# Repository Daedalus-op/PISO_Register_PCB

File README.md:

# PCB Designs
- [PISO Shift Register](./PISO_Shift_Registor/README.md)
- [Cascadable Full Adder](./Cascadable_Full_Adder/README.md)

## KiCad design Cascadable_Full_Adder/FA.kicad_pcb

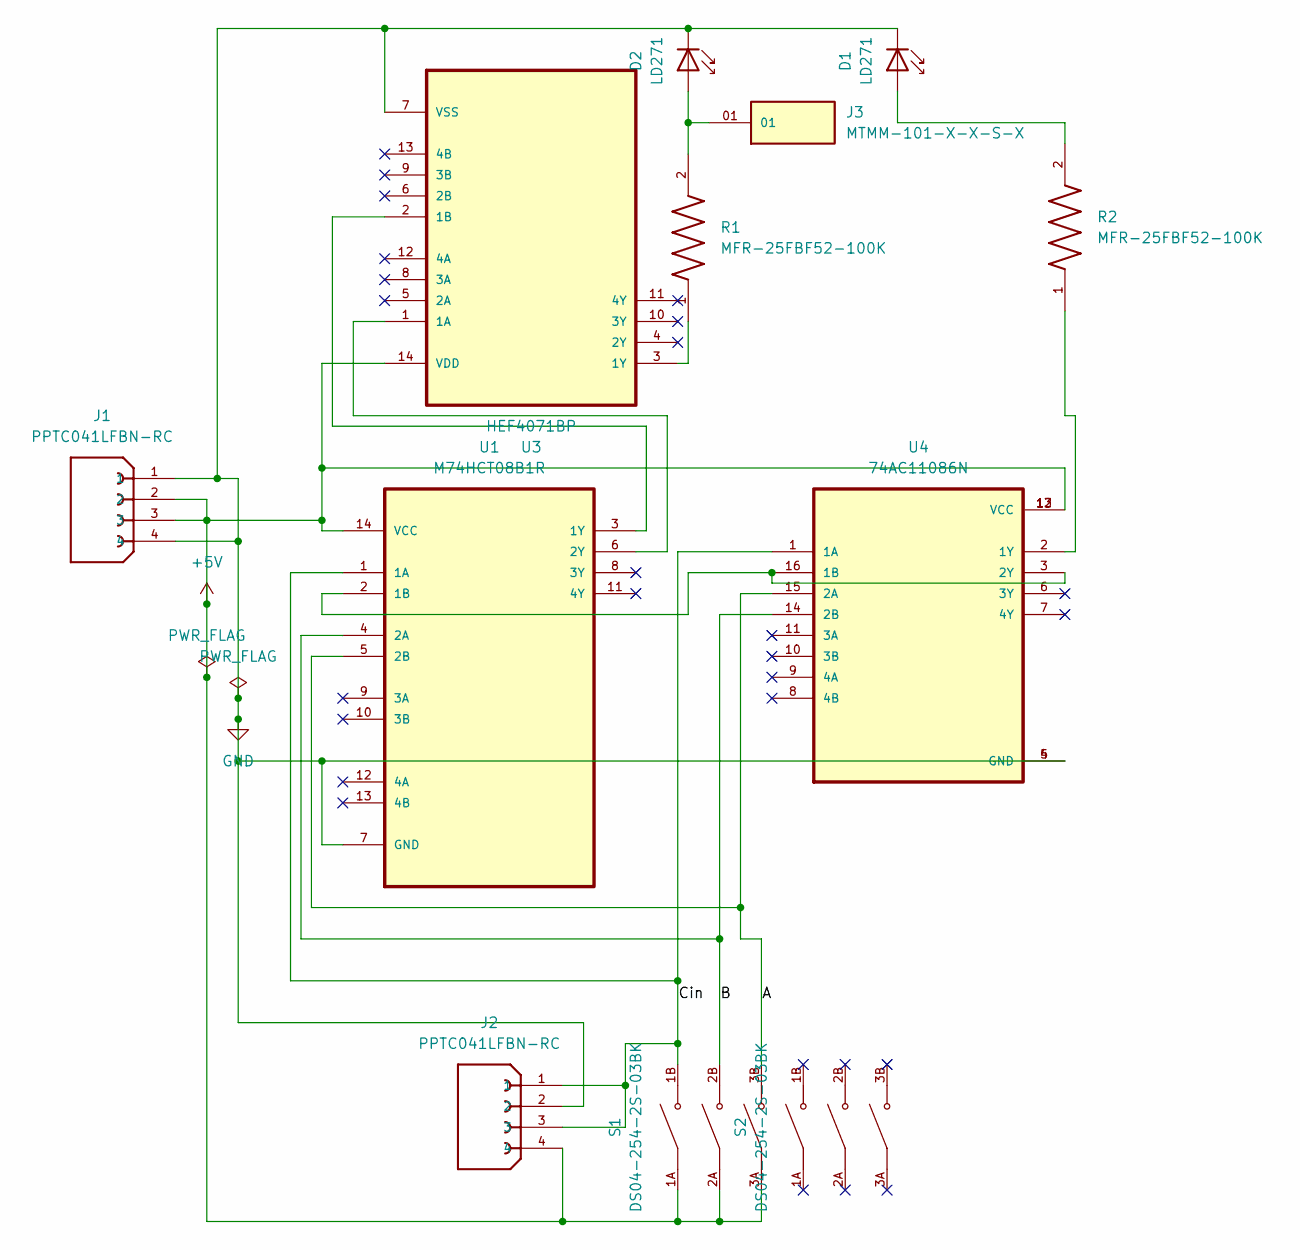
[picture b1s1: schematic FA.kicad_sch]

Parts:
D1, D2: LD271; LED_D5.0mm_IRGrey
J1, J2: PPTC041LFBN-RC; SULLINS_PPTC041LFBN-RC; PARTREV J - 04/15/2015
J3: MTMM-101-X-X-S-X; SAMTEC_MTMM-101-X-X-S-X; PARTREV 12-8-93
R1, R2: MFR-25FBF52-100K; RESAD1100W55L680D260; PARTREV 201304
S1, S2: DS04-254-2S-03BK; SW_DS04-254-2S-03BK; PARTREV V0.0
U1: M74HCT08B1R; DIP254P762X510-14; MPN M74HCT08B1R
U3: HEF4071BP; DIP254P762X420-14; MPN HEF4071BP
U4: 74AC11086N; DIP794W45P254L1969H508Q16

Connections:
+5V: J1.2, J1.3, J2.4, S1.1A, S1.2A, S1.3A, U1.14 (VCC), U3.14 (VDD), U4.12 (VCC), U4.13 (VCC)
/A: S1.3B, U1.5 (2B), U4.15 (2A)
/B: S1.2B, U1.4 (2A), U4.14 (2B)
/Cin: J2.1, J2.3, S1.1B, U1.1 (1A), U4.1 (1A)
GND: D1.1 (K), D2.1 (K), J1.1, J1.4, J2.2, U1.7 (GND), U3.7 (VSS), U4.4 (GND), U4.5 (GND)
unnamed: D1.2 (A), R2.2
unnamed: D2.2 (A), J3.01, R1.2
unnamed: U1.2 (1B), U4.3 (2Y), U4.16 (1B)
unnamed: U1.3 (1Y), U3.2 (1B)
unnamed: U1.6 (2Y), U3.1 (1A)
unnamed: R1.1, U3.3 (1Y)
unnamed: R2.1, U4.2 (1Y)

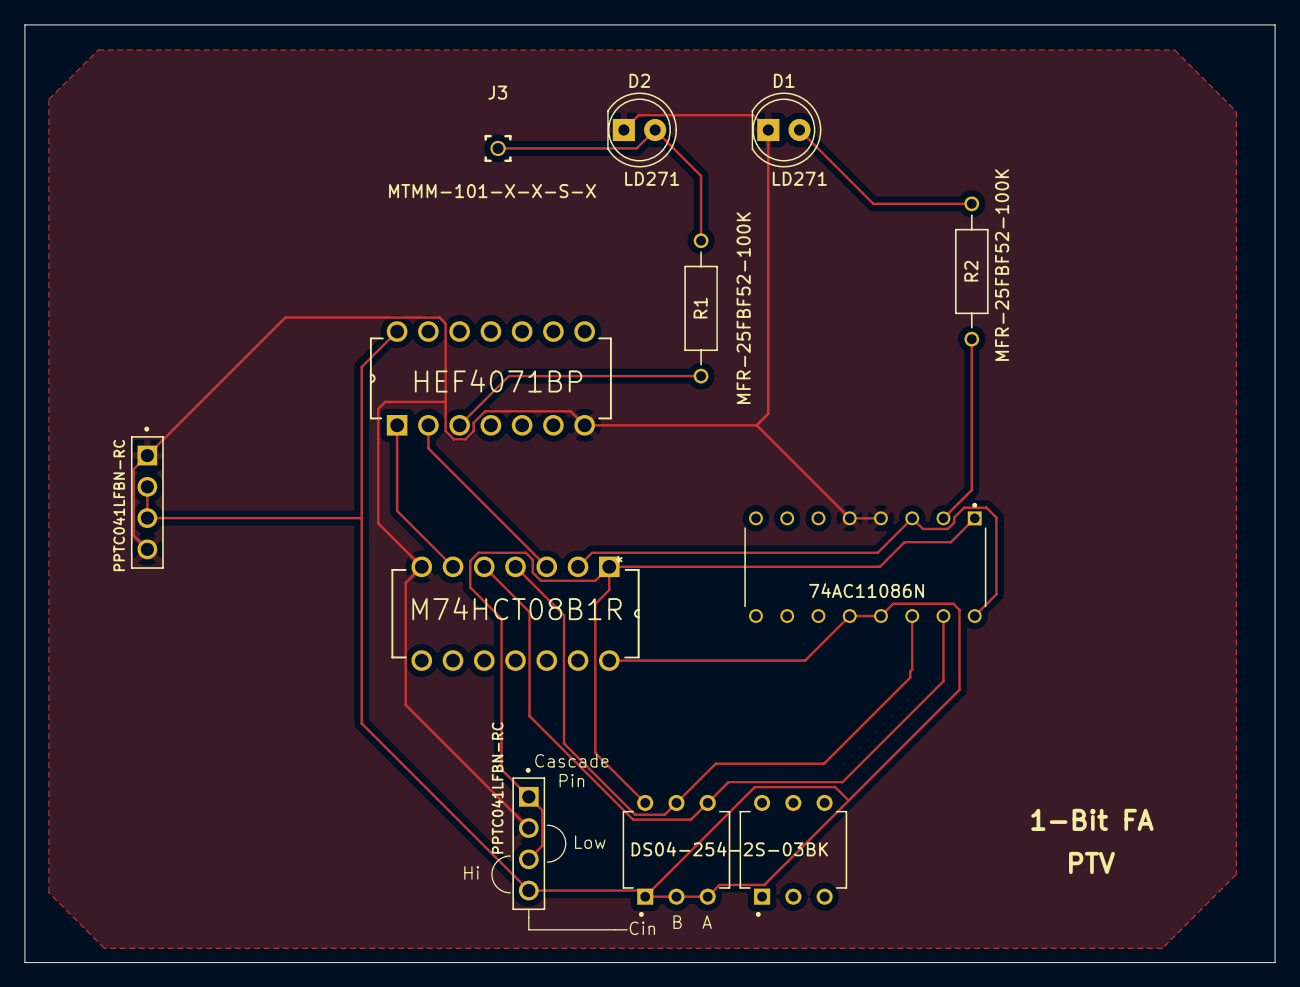
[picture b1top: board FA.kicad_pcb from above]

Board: 2 copper layers, 101.6 x 76.2 mm, 12 parts (0 on the bottom side), 12 nets.

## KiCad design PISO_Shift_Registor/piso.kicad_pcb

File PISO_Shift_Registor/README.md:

## PISO Register  
A PCB Implementation  
---
Materials used :-  
Resistor :- https://www.snapeda.com/parts/RP73D1J13RBTDG/TE%20Connectivity/view-part/?ref=search&t=resistor%200603  
Header pin :- https://www.snapeda.com/parts/PPTC041LFBN-RC/Sullins%20Connector/view-part/?ref=search&t=PPTC041LFBN-RC  
Array of Switches :- https://www.snapeda.com/parts/DS04-254-2-03BK-SMT/CUI%20Devices/view-part/?ref=search&t=DS04-254-2-03BK-SMT  
Dual D Flip - Flop :- https://www.snapeda.com/parts/CD4013BMT/Texas%20Instruments/view-part/?ref=search&t=CD4013BMT  
Quad 2:1 mux :- https://www.snapeda.com/parts/ADG794BRQZ-REEL7/Analog%20Devices/view-part/?ref=search&t=ADG794BRQZ  
Button switch :- https://www.snapeda.com/parts/1825910-6/TE%20Connectivity/view-part/?ref=search&t=1825910-6  

---
### Reference Schematic  
  
### Final schematic  
  
### PCB layout  
  
### PCB 3d Viewer (Front image)  
  
### PCB 3d Viewer (Back Image)

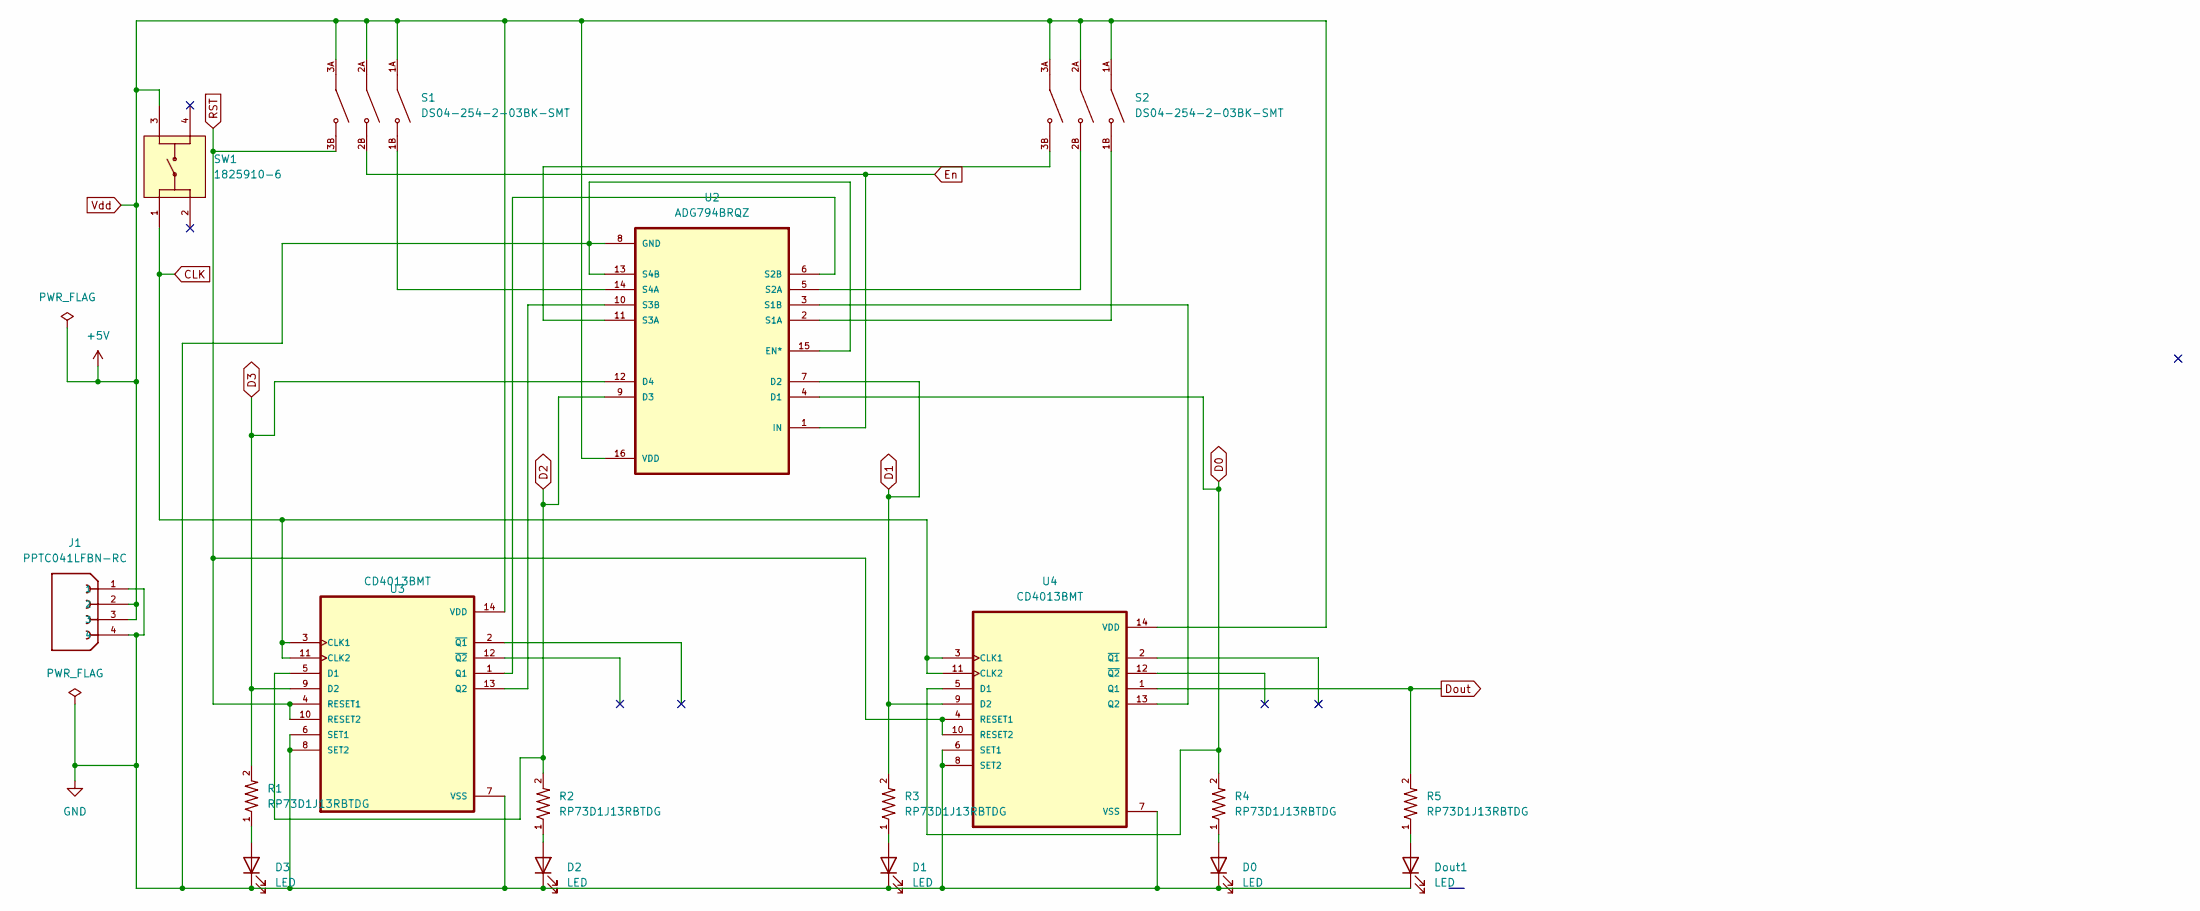
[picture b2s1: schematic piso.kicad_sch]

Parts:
D0, D1, D2, D3: LED; LED_D5.0mm
Dout1: LED; LED_D5.0mm
J1: PPTC041LFBN-RC; SULLINS_PPTC041LFBN-RC; PARTREV J - 04/15/2015
R1, R2, R3, R4, R5: RP73D1J13RBTDG; RESC1608X50N
S1, S2: DS04-254-2-03BK-SMT; SW_DS04-254-2-03BK-SMT; PARTREV V0.0
SW1: 1825910-6; SW_1825910-6-4; PARTREV C10
U2: ADG794BRQZ; SOP64P600X175-16N
U3, U4: CD4013BMT; SOIC127P600X175-14N

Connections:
CLK: SW1.1, U3.3 (CLK1), U3.11 (CLK2), U4.3 (CLK1), U4.11 (CLK2)
D0: R4.2, U2.4 (D1), U4.5 (D1)
D1: R3.2, U2.7 (D2), U4.9 (D2)
D2: R2.2, U2.9 (D3), U3.5 (D1)
D3: R1.2, U2.12 (D4), U3.9 (D2)
Dout: R5.2, U4.1 (Q1)
En: S1.2B, U2.1 (IN)
GND: D0.1 (K), D1.1 (K), D2.1 (K), D3.1 (K), Dout1.1 (K), J1.1, J1.4, U2.8 (GND), U2.13 (S4B), U2.15 (EN*), U3.6 (SET1), U3.7 (VSS), U3.8 (SET2), U4.6 (SET1), U4.7 (VSS), U4.8 (SET2)
unnamed: D0.2 (A), R4.1
unnamed: D1.2 (A), R3.1
unnamed: D2.2 (A), R2.1
unnamed: D3.2 (A), R1.1
unnamed: Dout1.2 (A), R5.1
unnamed: S2.1B, U2.2 (S1A)
unnamed: U2.3 (S1B), U4.13 (Q2)
unnamed: S2.2B, U2.5 (S2A)
unnamed: U2.6 (S2B), U3.1 (Q1)
unnamed: S2.3B, U2.11 (S3A)
unnamed: U2.10 (S3B), U3.13 (Q2)
unnamed: S1.1B, U2.14 (S4A)
RST: S1.3B, U3.4 (RESET1), U3.10 (RESET2), U4.4 (RESET1), U4.10 (RESET2)
Vdd: J1.2, J1.3, S1.1A, S1.2A, S1.3A, S2.1A, S2.2A, S2.3A, SW1.3, U2.16 (VDD), U3.14 (VDD), U4.14 (VDD)

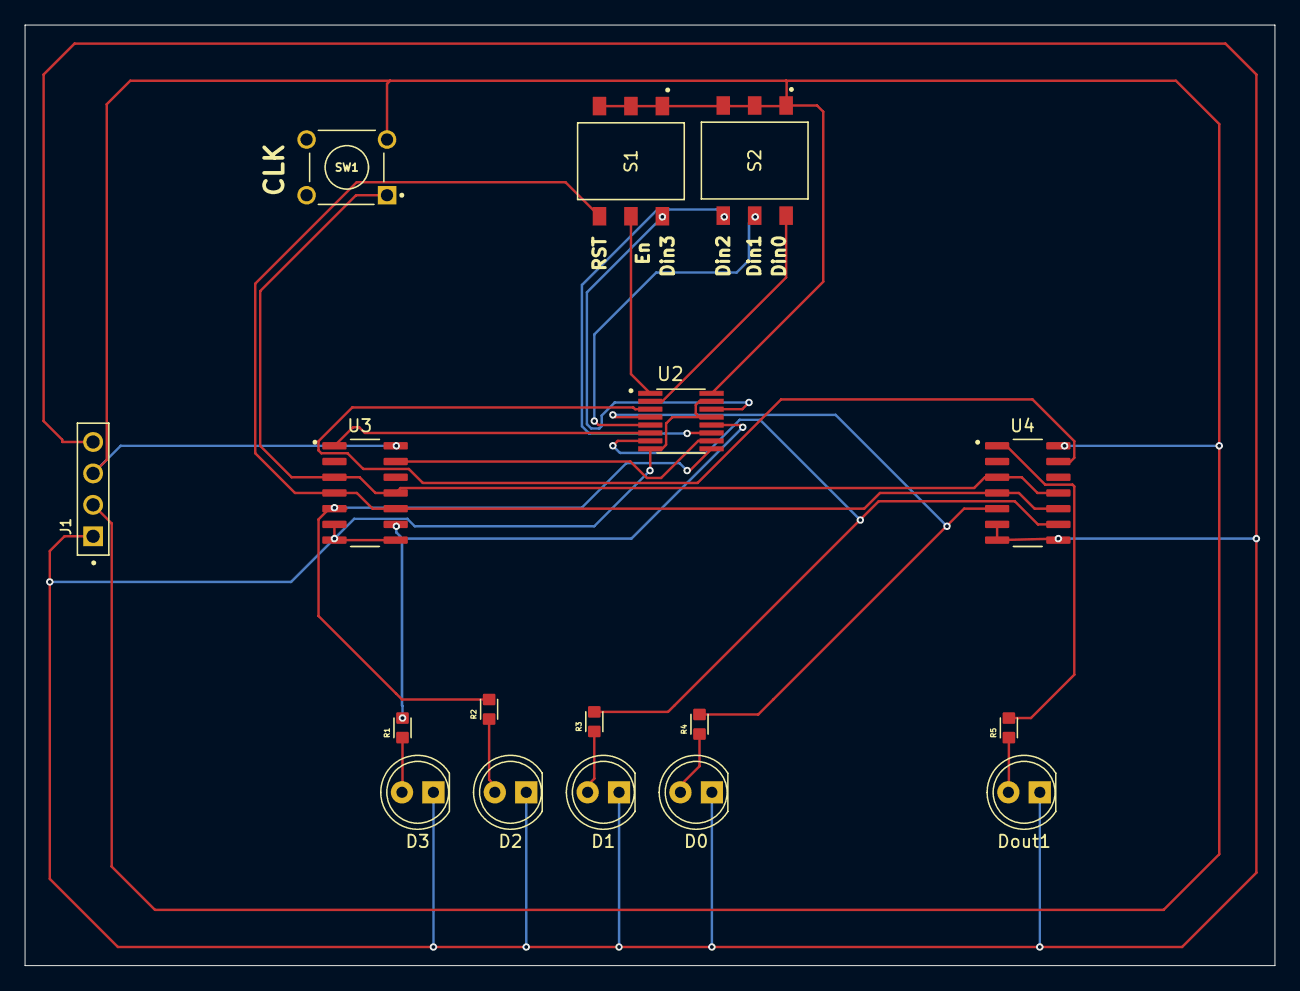
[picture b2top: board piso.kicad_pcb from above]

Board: 2 copper layers, 101.0 x 76.0 mm, 17 parts (0 on the bottom side), 22 nets.

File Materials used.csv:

"SL.No","Reference","Value","Datasheet","Footprint","Qty","DNP"
"1","D0,D1,D2,D3,Dout1","LED","~","LED_THT:LED_D5.0mm","5",""
"2","J1","PPTC041LFBN-RC","","PPTC041LFBN-RC:SULLINS_PPTC041LFBN-RC","1",""
"3","R1,R2,R3,R4,R5","RP73D1J13RBTDG","","RP73D1J13RBTDG:RESC1608X50N","5",""
"4","S1,S2","DS04-254-2-03BK-SMT","","DS04-254-2-03BK-SMT:SW_DS04-254-2-03BK-SMT","2",""
"5","SW1","1825910-6","","1825910-6:SW_1825910-6-4","1",""
"6","U2","ADG794BRQZ","","ADG794BRQZ:SOP64P600X175-16N","1",""
"7","U3,U4","CD4013BMT","","CD4013BMT:SOIC127P600X175-14N","2",""

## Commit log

2024-04-13 Initial Commit, Completed Version
2024-04-13 Added models used
2024-04-13 Added Readme file
2024-04-13 Updated GERBER Files
2024-04-13 Update README.md
    Materials used
2024-04-13 Updated all files
2024-04-13 Updated Materials used files
2024-04-13 Updated files
2024-06-24 Materials used
2025-01-28 Merged All PCB Designed
